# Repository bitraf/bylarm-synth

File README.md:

This is an analog synthesier, designed to be built as a 3-hour workshop by people new to electronics.
Made for [By:larm](http://www.bylarm.no/) Interactive in Oslo, 2014.

The project consists of both electronics, casing and tooling for applying solder paste. The project was produced on a standard Shopbot.
The electronics is mostly surface-mount technology and designed to be soldered using a reflow oven.

Credits
========
* Vidar Kristiansen
* [Jens Dyvik](http://dyvikdesign.com)
* Thomas Winther
* [Jon Nordby](http://jonnor.com)

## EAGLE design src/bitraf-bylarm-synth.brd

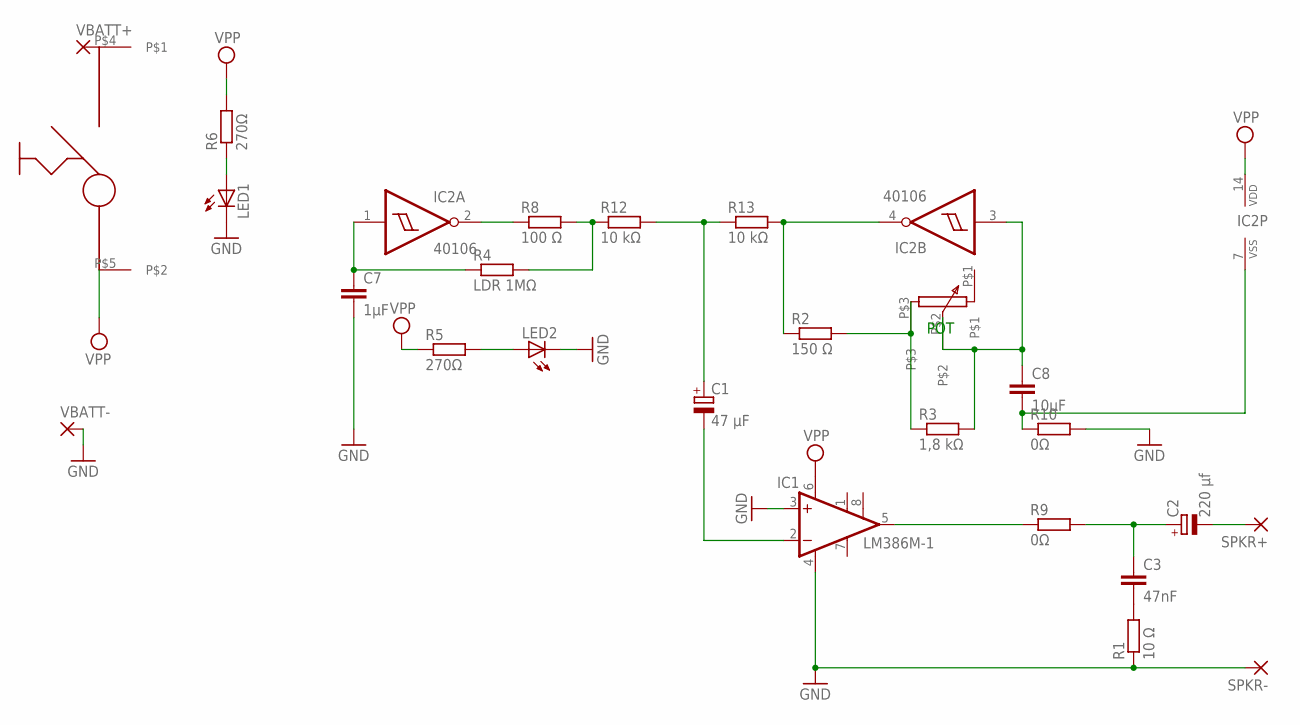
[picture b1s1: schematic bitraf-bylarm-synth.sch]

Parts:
C1: 47 µF; 153CLV-0605
C2: 220 µf; 153CLV-0605
C3: 47nF; C0402
C7: 1µF; C0603
C8: 10µF; C1206
IC1: LM386M-1; SO08
IC2: 40106; SO14
LED1: LED3MM
LED2: LEDP-LCC-2; P-LCC-2
R1: 10 Ω; R2512
R2: 150 Ω; R1206
R3: 1,8 kΩ; R1206
R4: LDR 1MΩ; 0204V
R5, R6: 270Ω; R2512
R8: 100 Ω; R1206
R9, R10: 0Ω; R1206
R12, R13: 10 kΩ; R1206
SPKR+: 1,6/0,9
SPKR-: 1,6/0,9
U$1: SMALLPOT
U$2: BYLARMSWITCH
VBATT+: 2,15/1,0
VBATT-: 2,15/1,0

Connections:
GND: C7.2, IC1.3 (+IN), IC1.4 (GND), LED1.K (C), LED2.C, R1.1, R10.2, SPKR-.1, VBATT-.1
unnamed: R4.2, R8.2, R12.1
unnamed: C2.+, C3.1, R9.2
unnamed: C1.-, IC1.2 (-IN)
unnamed: C3.2, R1.2
unnamed: R2.2, R3.1, U$1.P$3
unnamed: C8.1, IC2.3 (I), R3.2, U$1.P$2
unnamed: LED1.A, R6.1
unnamed: LED2.A, R5.2
unnamed: U$2.P$4, VBATT+.1
unnamed: C1.+, R12.2, R13.1
unnamed: C7.1, IC2.1 (I), R4.1
unnamed: C8.2, IC2.7 (VSS), R10.1
unnamed: IC1.5 (OUT), R9.1
unnamed: IC2.2 (O), R8.1
unnamed: IC2.4 (O), R2.1, R13.2
SPKR+: C2.-, SPKR+.1
VPP: IC1.6 (VS), IC2.14 (VDD), R5.1, R6.2, U$2.P$5

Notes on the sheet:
POT

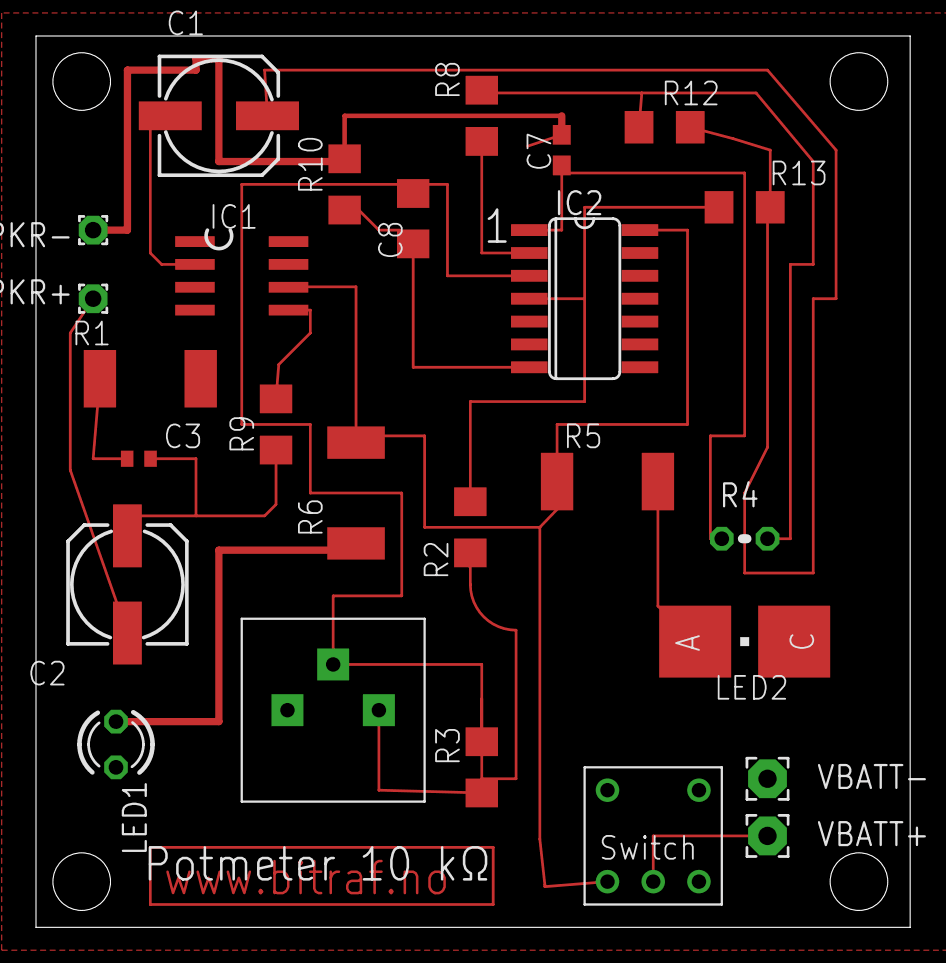
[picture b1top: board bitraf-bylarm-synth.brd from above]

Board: 2 copper layers, 48.6 x 49.5 mm, 26 parts (0 on the bottom side), 18 nets.

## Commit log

2014-02-25 Initial commitˍ
2014-02-25 Add Eagle project files for latest revisionx
2014-02-25 Add DXF export from Eagle
2014-02-25 Add a basic README
2014-02-26 Tweak schematics and layout for actual values used
2014-02-26 Add BOM list
2014-02-26 Add component outlines
2014-07-07 README: add links to personal websites
2014-07-07 doc: Add images of process/results
